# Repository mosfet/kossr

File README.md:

###KoSSR

A PWM controlled Solid State Relay. 8A at mains voltage, more with proper cooling, slightly based on the ACDimmer circuit by Robert Twomey (http://wiki.dxarts.washington.edu/groups/general/wiki/4dd69/AC_Dimmer_Circuit.html)

Originally designed to control a 120VAC 500W silicone heater mat for a 3d printer (http://github.com/mosfet/kossel-minimax)

The ATTiny45 reads an ADC pin sensing the PWM voltage from a control board, and a signal from the Zero-Cross sensing opto-isolator.

It uses these signals to control an opto-isolated triac (think mosfet for alternating current) in a controlled manner providing exact chopping of mains AC voltage.

Great for heating elements, dimming lightbulbs. More info can be found here: http://www.digikey.com/ca/en/techzone/lighting/resources/articles/Retrofit-LED-Bulbs-and-Drivers.html

**Basic BOM:**

Mouser Shopping Cart:

https://www.mouser.com/ProjectManager/ProjectDetail.aspx?AccessID=5bcadebf04

$6.39 for all parts except circuit board

*TODO:*

Add firmware support for 50hz and AREF comparison (rather than internal aref)

Hardware rc filter for PWM smoothing?

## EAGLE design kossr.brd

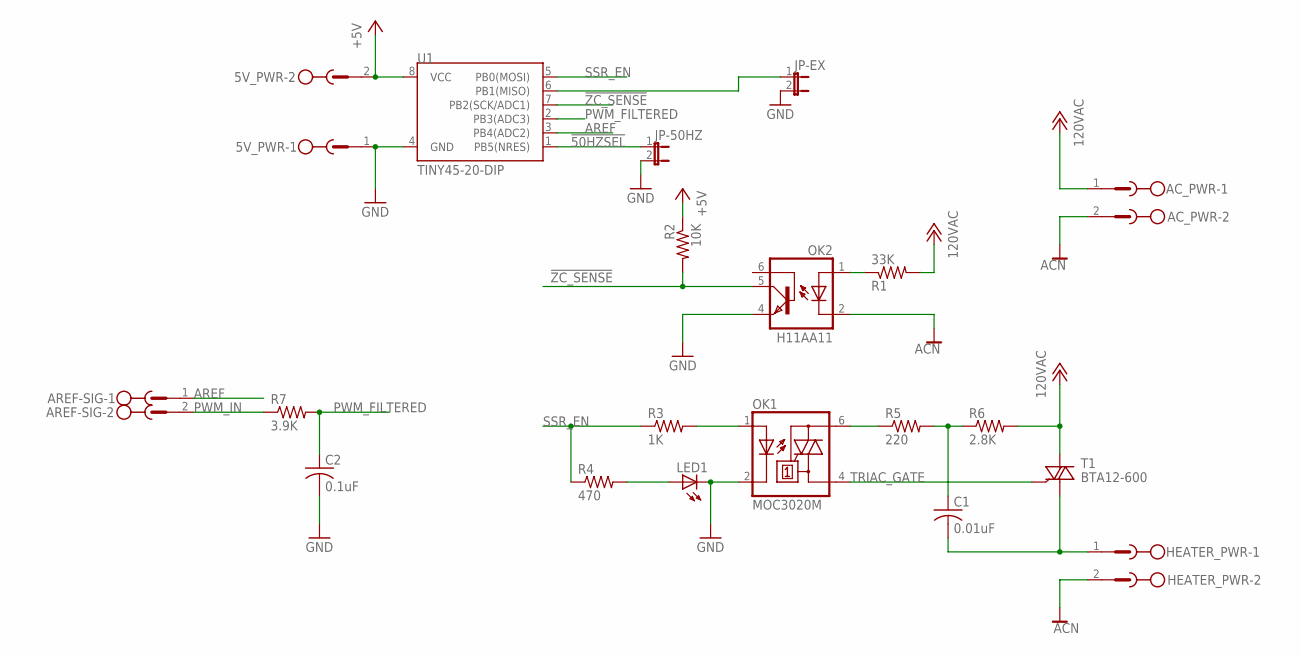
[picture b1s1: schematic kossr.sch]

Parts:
5V_PWR: MSTBV2
AC_PWR: MSTBV2
AREF-SIG: MSTBV2
C1: 0.01uF; C050-024X044
C2: 0.1uF; C025-024X044
HEATER_PWR: MSTBV2
JP-50HZ: JUMPER-2SMD-NO; SJ_2S-NO
JP-EX: JUMPER-2SMD-NO; SJ_2S-NO
LED1: LED3MM
OK1: MOC3020M; DIL06
OK2: H11AA11; DIL06
R1: 33K; 0207/7
R2: 10K; 0207/7
R3: 1K; 0207/7
R4: 470; 0207/7
R5: 220; 0207/7
R6: 2.8K; 0207/7
R7: 3.9K; 0207/7
T1: BTA12-600; TO220AB
U1: TINY45-20-DIP; DIP08

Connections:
!50HZSEL: JP-50HZ.1, U1.1 (PB5(NRES))
!EX: JP-EX.1, U1.6 (PB1(MISO))
!ZC_SENSE: OK2.5 (COL), R2.2, U1.7 (PB2(SCK/ADC1))
+5V: 5V_PWR.2, R2.1, U1.8 (VCC)
ACHOT: AC_PWR.1, R1.2, R6.2, T1.2 (A2)
ACN: AC_PWR.2, HEATER_PWR.2, OK2.2 (C)
AREF: AREF-SIG.1, U1.3 (PB4(ADC2))
GND: 5V_PWR.1, C2.2, JP-50HZ.2, JP-EX.2, LED1.K (C), OK1.2 (C), OK2.4 (EMI), U1.4 (GND)
HEATERHOT: C1.2, HEATER_PWR.1, T1.1 (A1)
unnamed: OK2.1 (A), R1.1
unnamed: LED1.A, R4.2
unnamed: OK1.1 (A), R3.2
unnamed: C1.1, R5.2, R6.1
unnamed: OK1.6 (A2), R5.1
PWM_FILTERED: C2.1, R7.2, U1.2 (PB3(ADC3))
PWM_IN: AREF-SIG.2, R7.1
SSR_EN: R3.1, R4.1, U1.5 (PB0(MOSI))
TRIAC_GATE: OK1.4 (A1), T1.3 (G)

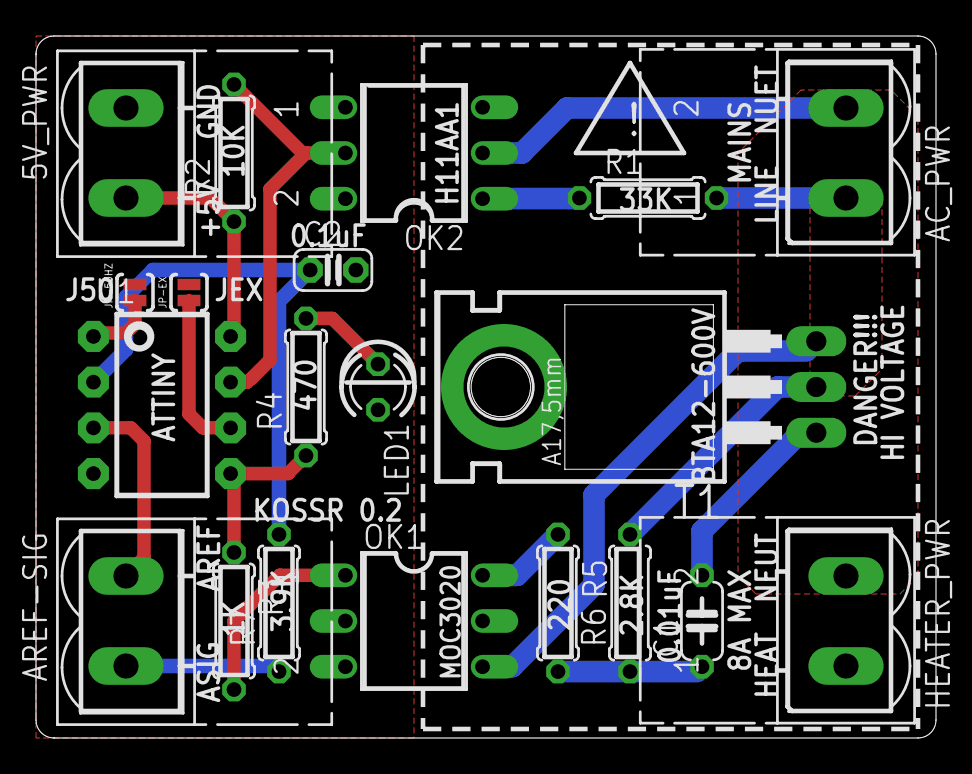
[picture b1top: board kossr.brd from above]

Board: 2 copper layers, 50.0 x 39.0 mm, 20 parts (0 on the bottom side), 18 nets.

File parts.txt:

Mouser Shopping Cart:
https://www.mouser.com/ProjectManager/ProjectDetail.aspx?Acc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
$6.39 for all parts except circuit board



Partlist

Exported from kossr.sch at 6/28/2014 7:56:33 PM

EAGLE Version 6.3.0 Copyright (c) 1988-2012 CadSoft

Assembly variant: 

Part       Value          Device                Package      Library            Sheet

5V_PWR                    MSTBV2                MSTBV2       con-phoenix-500    1
AC_PWR                    MSTBV2                MSTBV2       con-phoenix-500    1
AREF-SIG                  MSTBV2                MSTBV2       con-phoenix-500    1
C1         0.01uF         C-US050-024X044       C050-024X044 adafruit           1
HEATER_PWR                MSTBV2                MSTBV2       con-phoenix-500    1
JP-50HZ                   JUMPER-2SMD-NO        SJ_2S-NO     SparkFun-Retired   1
JP-EX                     JUMPER-2SMD-NO        SJ_2S-NO     SparkFun-Retired   1
LED1                      LED3MM                LED3MM       led                1
OK1        MOC3020M       MOC3020M              DIL06        optocoupler        1
OK2        H11AA11        H11AA11               DIL06        twomey             1
R1         33K            R-US_0207/7           0207/7       rcl                1
R2         10K            R-US_0207/7           0207/7       rcl                1
R3         1K             R-US_0207/7           0207/7       rcl                1
R4         470            R-US_0207/7           0207/7       rcl                1
R5         220            R-US_0207/7           0207/7       rcl                1
R6         2.8K           R-US_0207/7           0207/7       rcl                1
T1         BTA12-600      BTA12-600             TO220AB      twomey             1
U1         TINY45-20-DIP  ATTINY45TINY45-20-DIP DIP08        SparkFun-DigitalIC 1

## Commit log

2014-06-29 kossr Initial Checkin
2014-06-29 Add parts and images
2015-06-17 update to kossr 0.2
    adds input r/c filter

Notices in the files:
parts and their libraries:
SparkFun-DigitalIC: Licensing: Creative Commons ShareAlike 4.0 International - https://creativecommons.org/licenses/by-sa/4.0
